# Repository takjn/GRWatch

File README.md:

# GR-Watch
[KurumiWatch](https://github.com/takjn/KurumiWatch)を動かすための専用基板です。

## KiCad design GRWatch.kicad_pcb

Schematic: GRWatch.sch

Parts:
BT1: Battery_Cell; Keystone_3034_1x20mm-CoinCell
C1: 0.47uF; C_0805_HandSoldering
C2: 0.1uF; C_0805_HandSoldering
C3, C4: 15pF; C_0805_HandSoldering
C5, C6: 1.0uF; C_0805_HandSoldering
C7, C8: 2.2uF; C_0805_HandSoldering
J1: JST_SH_06; JST-SM-06B-SRSS-TB
J2: JST_SH_04; JST-SM-04B-SRSS-TB
R1: 1k; R_0805_HandSoldering
R2: 12k; R_0805_HandSoldering
R3: 2k; R_0805_HandSoldering
R4: 400k; R_0805_HandSoldering
SW1, SW2, SW3: SW_Push; THAM16
U1: R5F100LJAFB; LQFP-64_10x10mm_Pitch0.5mm
U2: BUZZER; BZ7025_3pin
U3: SSD1306
Y1: 32.768k; Crystal_SMD_G8-2pin_3.2x1.5mm_HandSoldering

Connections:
+3V3: BT1.1 (+), C2.1, J1.4, R1.1, R2.1, U1.15 (VDD), U1.16 (EVDD0), U1.56 (P20/ANI0/AVREFP), U3.6 (VBAT), U3.9 (VDD), U3.11 (BS1), U3.14 (/RES)
A0: J2.2, U1.54 (P22/ANI2)
A1: J2.1, U1.53 (P23/ANI3)
CTS: J1.5, R2.2, R3.1, U1.5 (P40/TOOL0)
D7: J2.4, U1.60 (P02/ANI17/SO10/TxD1)
D8: J2.3, U1.59 (P03/ANI16/SI10/RxD1/SDA10)
DTR: J1.1, R1.2, U1.6 (~RESET)
GND: BT1.2 (-), C1.2, C2.2, C3.2, C4.2, C7.2, C8.2, J1.6, R4.2, SW1.2, SW2.2, SW3.2, U1.9 (P137/INTP0), U1.10 (P122/X2/EXCLK), U1.11 (P121/X1), U1.13 (VSS), U1.14 (EVSS0), U1.55 (P21/ANI1/AVREFM), U2.2 (-), U3.8 (VSS), U3.10 (BS0), U3.12 (BS2), U3.13 (/CS), U3.15 (DC/I2C_SA0), U3.16 (R/W), U3.17 (E/RD), U3.21 (D3), U3.22 (D4), U3.23 (D5), U3.24 (D6), U3.25 (D7), U3.29 (VLSS)
unnamed: C1.1, U1.12 (REGC)
unnamed: C3.1, U1.7 (P124/XT2/EXCLKS), Y1.1
unnamed: C4.1, U1.8 (P123/XT1), Y1.2
unnamed: C5.1, U3.2 (C2P)
unnamed: C5.2, U3.3 (C2N)
unnamed: C6.1, U3.4 (C1P)
unnamed: C6.2, U3.5 (C1N)
unnamed: C7.1, U3.27 (VCOMH)
unnamed: C8.1, U3.28 (VCC)
unnamed: R4.1, U3.26 (IREF)
unnamed: U1.42 (P14/RxD2/SI20/SDA20/(SCLA0)/(TI03)/(TO0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), U2.1 (+)
RXD: J1.2, U1.44 (P12/SO00/TxD0/TOOLTxD/(INTP5)/(TI05)/(T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)
SCL: U1.17 (P60/SCLA0), U3.18 (D0/SPI_SCLK)
SDA: U1.18 (P61/SDAA0), U3.19 (D1/SPI_SDIN), U3.20 (D2/I2C_SDA)
SW1: SW1.1, U1.32 (P30/INTP3/RTC1HZ/SCK11/SCL11)
SW2: SW2.1, U1.40 (P16/TI01/TO01/INTP5/(SI00)/(RXD0))
SW3: SW3.1, U1.21 (P31/TI03/TO03/INTP4/(PCLBUZ0))
TXD: J1.3, R3.2, U1.45 (P11/SI00/RxD0/TOOLRXD/SDA00/(TI06)/(TO0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)

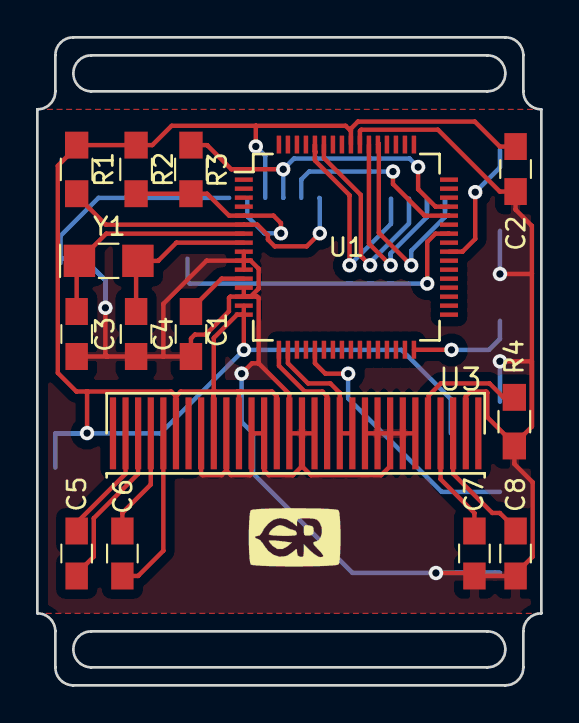
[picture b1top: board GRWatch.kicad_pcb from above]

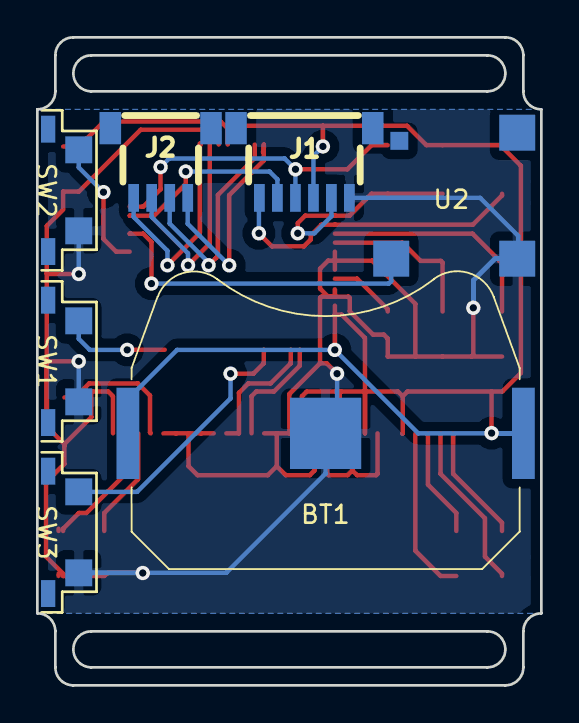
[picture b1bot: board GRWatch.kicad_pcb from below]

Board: 2 copper layers, 28.0 x 36.0 mm, 22 parts (7 on the bottom side), 26 nets.

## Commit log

2018-05-01 init
2018-05-01 remove unnecessary files
2018-05-03 add tiny version
2018-05-19 bug fix
